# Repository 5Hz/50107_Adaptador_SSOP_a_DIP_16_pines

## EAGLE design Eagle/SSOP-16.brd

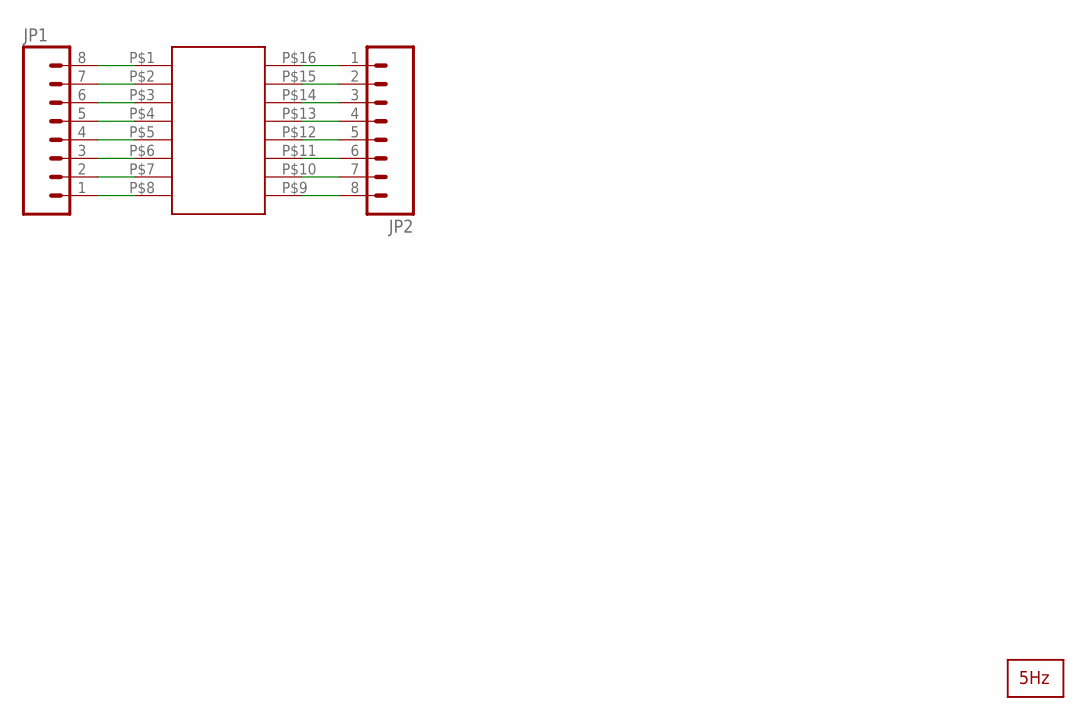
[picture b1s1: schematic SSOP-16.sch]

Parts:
JP1, JP2: M081X08; 1X08
U$1: SSOP-16SSOP-16; SSOP-16
U$2: LOGO2_SILK5MM; LOGO2_5MM

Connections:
unnamed: JP1.1, U$1.P$8
unnamed: JP1.2, U$1.P$7
unnamed: JP1.3, U$1.P$6
unnamed: JP1.4, U$1.P$5
unnamed: JP1.5, U$1.P$4
unnamed: JP1.6, U$1.P$3
unnamed: JP1.7, U$1.P$2
unnamed: JP1.8, U$1.P$1
unnamed: JP2.1, U$1.P$16
unnamed: JP2.2, U$1.P$15
unnamed: JP2.3, U$1.P$14
unnamed: JP2.4, U$1.P$13
unnamed: JP2.5, U$1.P$12
unnamed: JP2.6, U$1.P$11
unnamed: JP2.7, U$1.P$10
unnamed: JP2.8, U$1.P$9

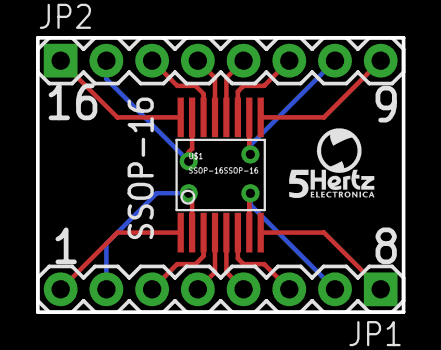
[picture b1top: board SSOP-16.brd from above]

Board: 2 copper layers, 20.3 x 15.2 mm, 4 parts (0 on the bottom side), 16 nets.

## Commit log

2014-01-14 creación

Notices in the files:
parts and their libraries:
SparkFun: Licensing: CC v3.0 Share-Alike You are welcome to use this library for commercial purposes.
